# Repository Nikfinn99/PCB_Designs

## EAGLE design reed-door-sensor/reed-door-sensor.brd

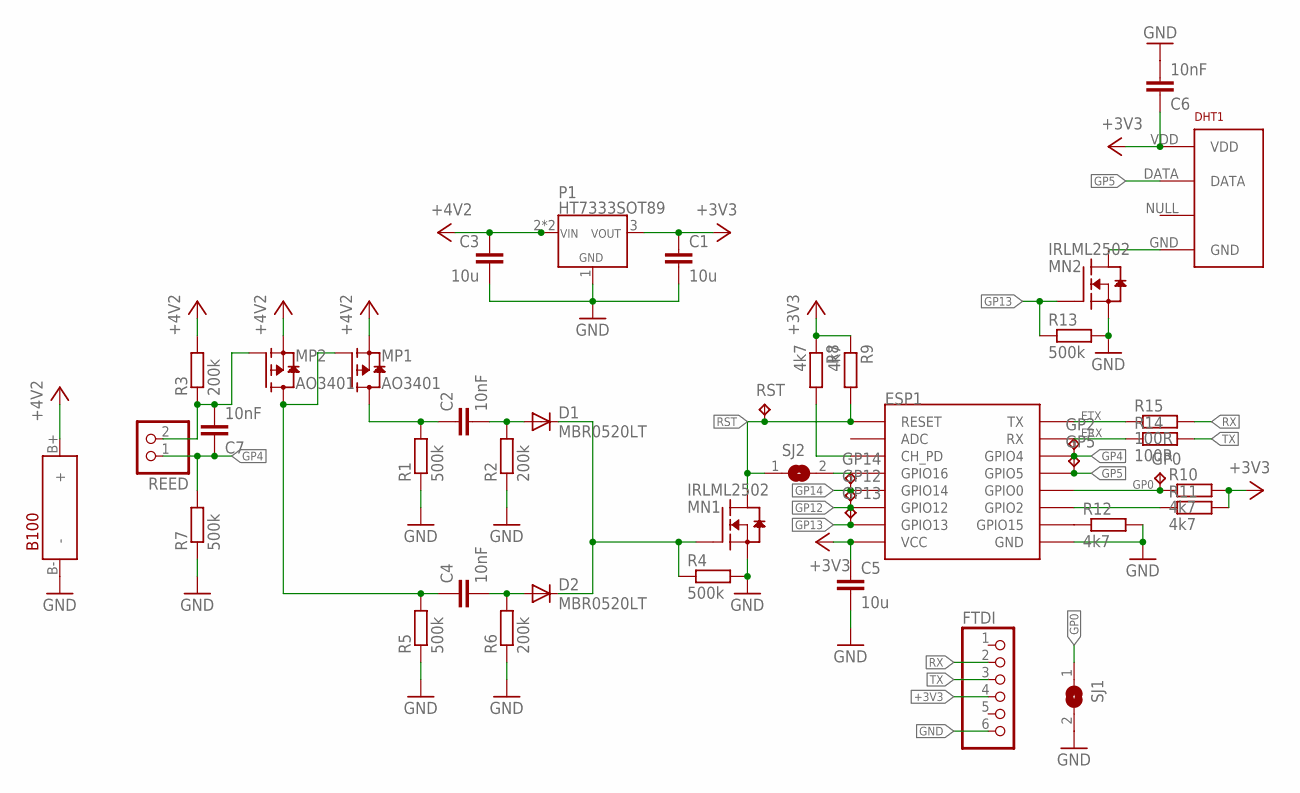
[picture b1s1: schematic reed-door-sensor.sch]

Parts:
B100: 18650_1X; 18650_HOLDER_1X
C1, C3, C5: 10u; C1206
C2, C4, C6, C7: 10nF; C0805
D1, D2: MBR0520LT; SOD123
DHT1: RHT03_DHT-22_AM2302; RHT03_DHT-22
ESP1: ESP12SMD; ESP12-SMD
FTDI: PINHD-1X06_2.54-S; 1X06-S
GP0: TPB2,54; B2,54
GP2, GP5, GP12, GP13, GP14: TPB1,27; B1,27
MN1, MN2: IRLML2502; SOT23
MP1, MP2: AO3401; SOT23
P1: HT7333SOT89; SOT89
R1, R4, R5, R7, R13: 500k; M0805
R2, R3, R6: 200k; M0805
R8, R9, R10, R11, R12: 4k7; M0805
R14, R15: 100R; M0805
REED: PINHD-1X02_2.54; 1X02
RST: TPB2,54; B2,54
SJ1, SJ2: SJ

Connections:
+3V3: C1.1, C5.1, C6.1, DHT1.VDD, ESP1.VCC, FTDI.4, P1.3 (VOUT), R8.1, R9.1, R10.2, R11.2
+5V: B100.B+ (+), C3.1, MP1.2 (S), MP2.2 (S), P1.2 (VIN), P1.2@1 (VIN), R3.2
ERX: ESP1.RXD0 (RX), R14.1
ETX: ESP1.TXD0 (TX), R15.1
GND: B100.B- (-), C1.2, C3.2, C5.2, C6.2, ESP1.GND, FTDI.6, MN1.2 (S), MN2.2 (S), P1.1 (GND), R1.1, R2.1, R4.2, R5.1, R6.1, R7.1, R12.2, R13.2, SJ1.2
GP0: ESP1.GPIO0, GP0.TP, R10.1, SJ1.1
GP4: C7.1, ESP1.GPIO4, GP2.TP, R7.2, REED.1
GP5: DHT1.DATA, ESP1.GPIO5, GP5.TP
GP12: ESP1.GPIO12, GP12.TP
GP13: ESP1.GPIO13, GP13.TP, MN2.1 (G), R13.1
GP14: ESP1.GPIO14, GP14.TP
unnamed: ESP1.GPIO16, SJ2.2
unnamed: ESP1.CH_PD, R8.2
unnamed: C2.2, D1.A, R2.2
unnamed: ESP1.GPIO15, R12.1
unnamed: ESP1.GPIO2, R11.1
unnamed: C4.2, D2.A, R6.2
unnamed: C2.1, MP1.3 (D), R1.2
unnamed: C4.1, MP1.1 (G), MP2.3 (D), R5.2
unnamed: D1.C, D2.C, MN1.1 (G), R4.1
unnamed: DHT1.GND, MN2.3 (D)
unnamed: C7.2, MP2.1 (G), R3.1, REED.2
RST: ESP1.RESET, MN1.3 (D), R9.2, RST.TP, SJ2.1
RX: FTDI.2, R15.2
TX: FTDI.3, R14.2

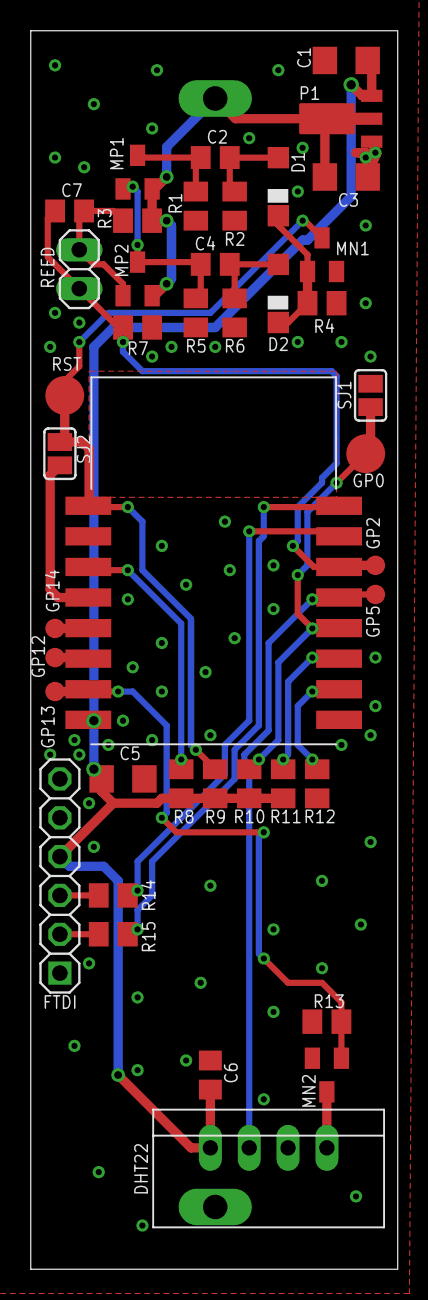
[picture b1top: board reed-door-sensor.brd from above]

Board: 2 copper layers, 24.0 x 81.0 mm, 43 parts (1 on the bottom side), 25 nets.

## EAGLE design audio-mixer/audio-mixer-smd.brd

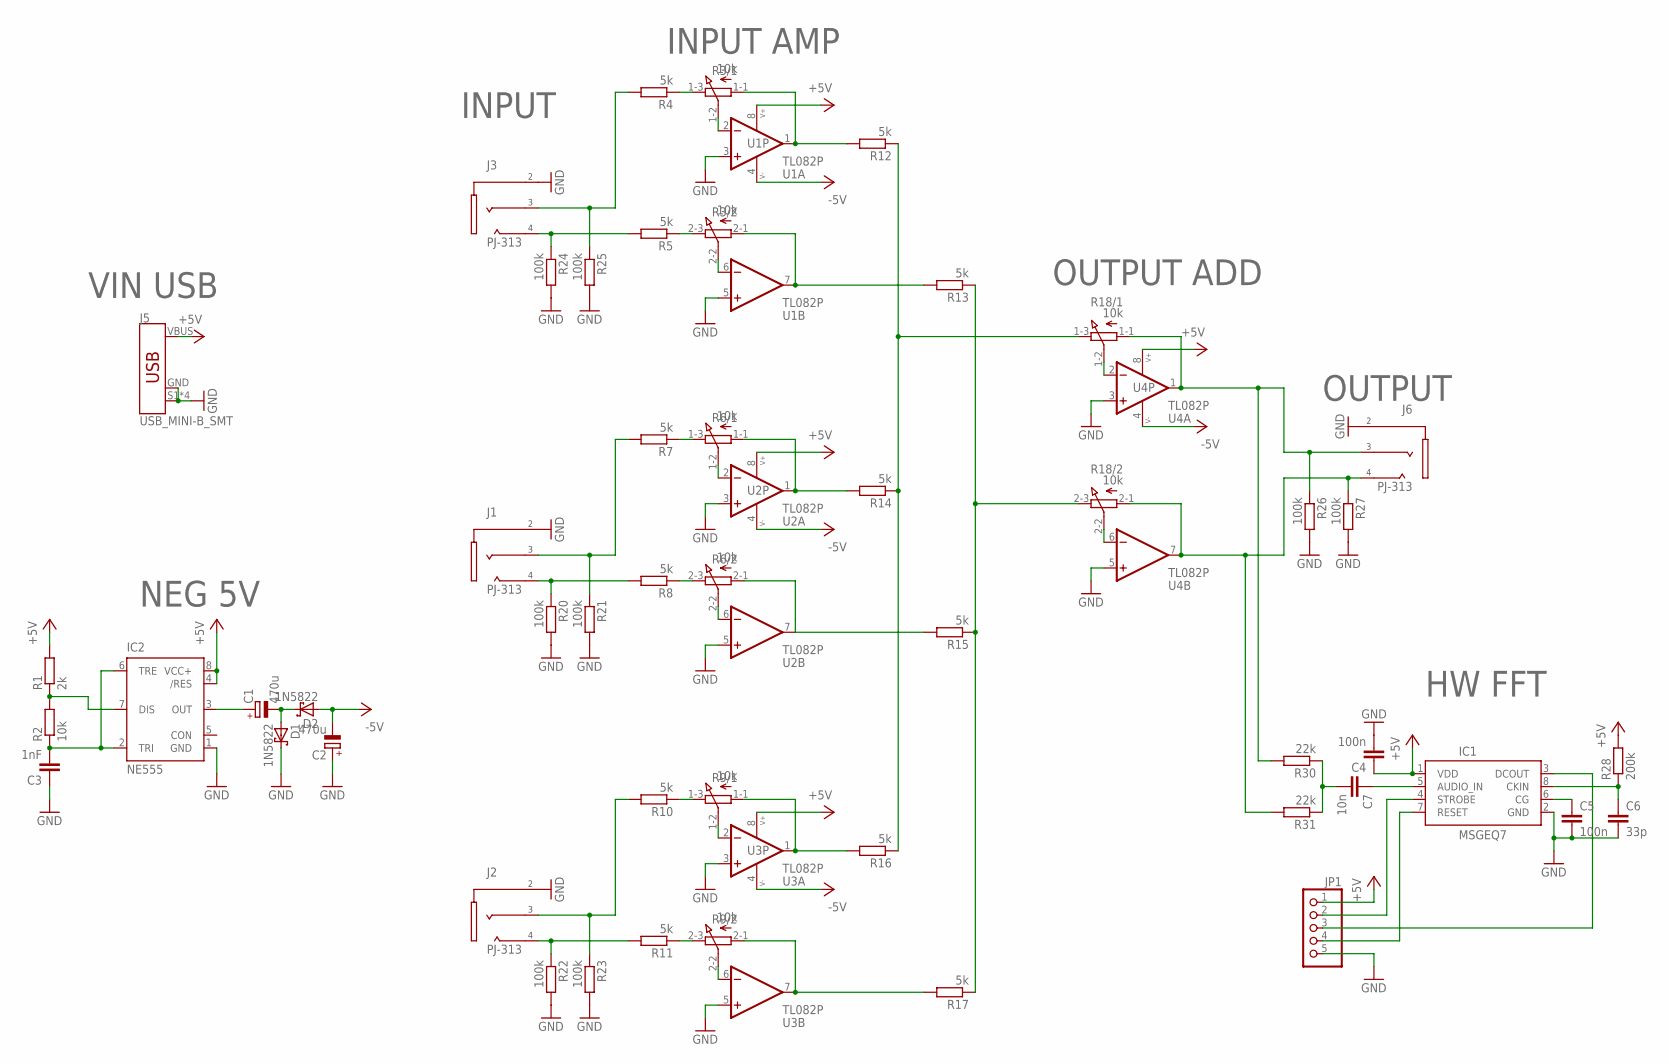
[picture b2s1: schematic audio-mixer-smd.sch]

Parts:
C1, C2: 470u; E5-8,5
C3: 1nF; C0805
C4, C5: 100n; C0805
C6: 33p; C0805
C7: 10n; C0805
D1, D2: 1N5822; DO41-7.6
IC1: MSGEQ7DIP; DIL08
IC2: NE555; DIL-08
J1, J2, J3, J6: PJ-313
J5: USB_MINI-B_SMT; USB-MINIB
JP1: PINHD-1X05_2.54-S; 1X05-S
R1: 2k; R0805
R2: 10k; R0805
R3, R6, R9, R18: 10k; 3RP/1610G
R4, R5, R7, R8, R10, R11, R12, R13, R14, R15, R16, R17: 5k; R0805
R20, R21, R22, R23, R24, R25, R26, R27: 100k; R0805
R28: 200k; R0805
R30, R31: 22k; R0805
U1, U2, U3, U4: TL082P; DIL08

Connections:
+5V: C4.1, IC1.1 (VDD), IC2.4 (/RES), IC2.8 (VCC+), J5.VBUS, JP1.1, R1.2, R28.2, U1.8 (V+), U2.8 (V+), U3.8 (V+), U4.8 (V+)
-5V: C2.-, D2.A, U1.4 (V-), U2.4 (V-), U3.4 (V-), U4.4 (V-)
GND: C2.+, C3.1, C4.2, C5.2, C6.2, D1.C, IC1.2 (GND), IC2.1 (GND), J1.2_1 (2), J1.2_2 (2), J2.2_1 (2), J2.2_2 (2), J3.2_1 (2), J3.2_2 (2), J5.GND, J5.S1 (SHIELD), J5.S2 (SHIELD), J5.S3 (SHIELD), J5.S4 (SHIELD), J6.2_1 (2), J6.2_2 (2), JP1.5, R20.2, R21.2, R22.2, R23.2, R24.2, R25.2, R26.2, R27.2, U1.3 (+IN), U1.5 (+IN), U2.3 (+IN), U2.5 (+IN), U3.3 (+IN), U3.5 (+IN), U4.3 (+IN), U4.5 (+IN)
unnamed: C3.2, IC2.2 (TRI), IC2.6 (TRE), R2.1
unnamed: IC2.7 (DIS), R1.1, R2.2
unnamed: R3.1-1 (A), R12.2, U1.1 (OUT)
unnamed: C1.-, D1.A, D2.C
unnamed: C1.+, IC2.3 (OUT)
unnamed: R3.1-2 (S), U1.2 (-IN)
unnamed: R3.2-1 (A), R13.2, U1.7 (OUT)
unnamed: R3.2-2 (S), U1.6 (-IN)
unnamed: R3.2-3 (E), R5.1
unnamed: R3.1-3 (E), R4.1
unnamed: J3.4_1 (4), J3.4_2 (4), R5.2, R24.1
unnamed: J3.3, R4.2, R25.1
unnamed: R6.1-1 (A), R14.2, U2.1 (OUT)
unnamed: R6.1-2 (S), U2.2 (-IN)
unnamed: R6.2-1 (A), R15.2, U2.7 (OUT)
unnamed: R6.2-2 (S), U2.6 (-IN)
unnamed: R6.2-3 (E), R8.1
unnamed: R6.1-3 (E), R7.1
unnamed: J1.4_1 (4), J1.4_2 (4), R8.2, R20.1
unnamed: J1.3, R7.2, R21.1
unnamed: R9.1-1 (A), R16.2, U3.1 (OUT)
unnamed: R9.1-2 (S), U3.2 (-IN)
unnamed: R9.2-1 (A), R17.2, U3.7 (OUT)
unnamed: R9.2-2 (S), U3.6 (-IN)
unnamed: R9.2-3 (E), R11.1
unnamed: R9.1-3 (E), R10.1
unnamed: J2.4_1 (4), J2.4_2 (4), R11.2, R22.1
unnamed: J2.3, R10.2, R23.1
unnamed: R12.1, R14.1, R16.1, R18.1-3 (E)
unnamed: R13.1, R15.1, R17.1, R18.2-3 (E)
unnamed: J6.3, R18.1-1 (A), R26.1, R30.2, U4.1 (OUT)
unnamed: J6.4_1 (4), J6.4_2 (4), R18.2-1 (A), R27.1, R31.2, U4.7 (OUT)
unnamed: R18.2-2 (S), U4.6 (-IN)
unnamed: R18.1-2 (S), U4.2 (-IN)
unnamed: C5.1, IC1.6 (CG)
unnamed: C6.1, IC1.8 (CKIN), R28.1
unnamed: C7.1, IC1.5 (AUDIO_IN)
unnamed: C7.2, R30.1, R31.1
unnamed: IC1.4 (STROBE), JP1.2
unnamed: IC1.7 (RESET), JP1.4
unnamed: IC1.3 (DCOUT), JP1.3

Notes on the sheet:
VIN USB
NEG 5V
INPUT AMP
OUTPUT ADD
OUTPUT
INPUT
HW FFT

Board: 2 copper layers, 50 parts (0 on the bottom side), 44 nets, no tracks yet.

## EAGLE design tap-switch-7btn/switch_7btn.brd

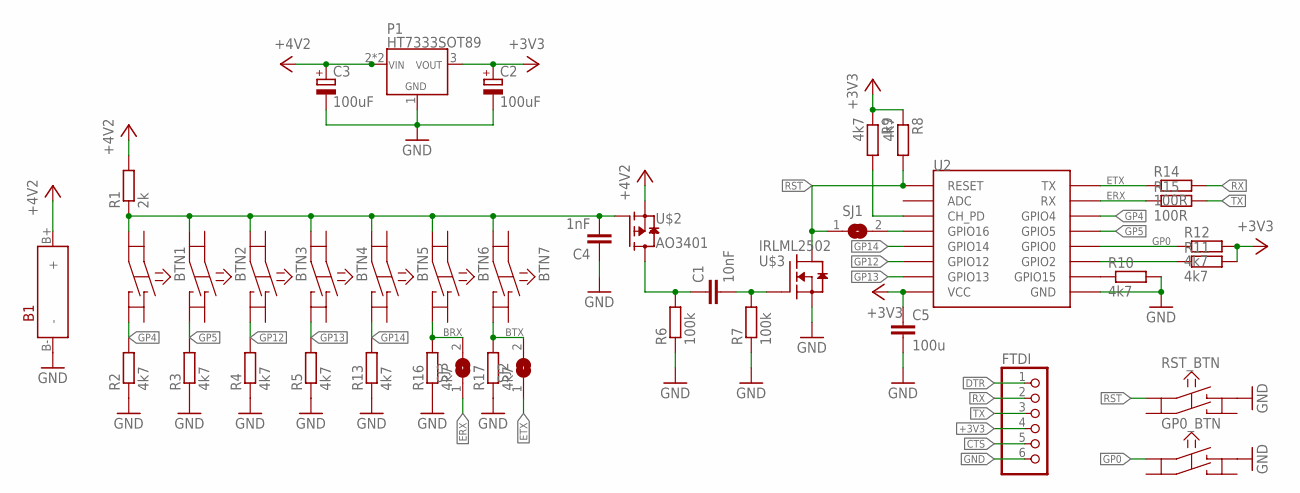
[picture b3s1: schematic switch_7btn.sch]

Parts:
B1: 18650_1X; 18650_HOLDER_1X
BTN1, BTN2, BTN3, BTN4, BTN5, BTN6, BTN7: KSM611A
C1: 10nF; C025-025X050
C2, C3: 100uF; E5-8,5
C4: 1nF; C025-025X050
C5: 100u; C1206
FTDI: PINHD-1X06_2.54-S; 1X06-S
GP0_BTN: KSM611A
P1: HT7333SOT89; SOT89
R1: 2k; MULTI_RESISTOR
R2, R3, R4, R5, R8, R9, R10, R11, R12, R13, R16, R17: 4k7; MULTI_RESISTOR
R6, R7: 100k; MULTI_RESISTOR
R14, R15: 100R; MULTI_RESISTOR
RST_BTN: KSM611A
SJ1, SJ2, SJ3: SJ
U2: ESP12SMD; ESP12-SMD
U$2: AO3401; SOT23
U$3: IRLML2502; SOT23

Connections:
+3V3: C2.+, C5.1, FTDI.4, P1.3 (VOUT), R8.1@1 (1), R8.1@2 (1), R9.1@1 (1), R9.1@2 (1), R11.2@1 (2), R11.2@2 (2), R12.2@1 (2), R12.2@2 (2), U2.VCC
+5V: B1.B+ (+), C3.+, P1.2 (VIN), P1.2@1 (VIN), R1.2@1 (2), R1.2@2 (2), U$2.2 (S)
BRX: BTN6.D, R16.2@1 (2), R16.2@2 (2), SJ3.2
BTX: BTN7.D, R17.2@1 (2), R17.2@2 (2), SJ2.2
CTS: FTDI.5
DTR: FTDI.1
ERX: R15.1@1 (1), R15.1@2 (1), SJ3.1, U2.RXD0 (RX)
ETX: R14.1@1 (1), R14.1@2 (1), SJ2.1, U2.TXD0 (TX)
GND: B1.B- (-), C2.-, C3.-, C4.1, C5.2, FTDI.6, GP0_BTN.B, P1.1 (GND), R2.1@1 (1), R2.1@2 (1), R3.1@1 (1), R3.1@2 (1), R4.1@1 (1), R4.1@2 (1), R5.1@1 (1), R5.1@2 (1), R6.1@1 (1), R6.1@2 (1), R7.1@1 (1), R7.1@2 (1), R10.2@1 (2), R10.2@2 (2), R13.1@1 (1), R13.1@2 (1), R16.1@1 (1), R16.1@2 (1), R17.1@1 (1), R17.1@2 (1), RST_BTN.B, U2.GND, U$3.2 (S)
GP0: GP0_BTN.A, R12.1@1 (1), R12.1@2 (1), U2.GPIO0
GP4: BTN1.D, R2.2@1 (2), R2.2@2 (2), U2.GPIO4
GP5: BTN2.D, R3.2@1 (2), R3.2@2 (2), U2.GPIO5
GP12: BTN3.D, R4.2@1 (2), R4.2@2 (2), U2.GPIO12
GP13: BTN4.D, R5.2@1 (2), R5.2@2 (2), U2.GPIO13
GP14: BTN5.D, R13.2@1 (2), R13.2@2 (2), U2.GPIO14
unnamed: SJ1.2, U2.GPIO16
unnamed: R9.2@1 (2), R9.2@2 (2), U2.CH_PD
unnamed: C1.2, R7.2@1 (2), R7.2@2 (2), U$3.1 (G)
unnamed: R10.1@1 (1), R10.1@2 (1), U2.GPIO15
unnamed: R11.1@1 (1), R11.1@2 (1), U2.GPIO2
unnamed: C1.1, R6.2@1 (2), R6.2@2 (2), U$2.3 (D)
unnamed: BTN1.C, BTN2.C, BTN3.C, BTN4.C, BTN5.C, BTN6.C, BTN7.C, C4.2, R1.1@1 (1), R1.1@2 (1), U$2.1 (G)
RST: R8.2@1 (2), R8.2@2 (2), RST_BTN.A, SJ1.1, U2.RESET, U$3.3 (D)
RX: FTDI.2, R14.2@1 (2), R14.2@2 (2)
TX: FTDI.3, R15.2@1 (2), R15.2@2 (2)

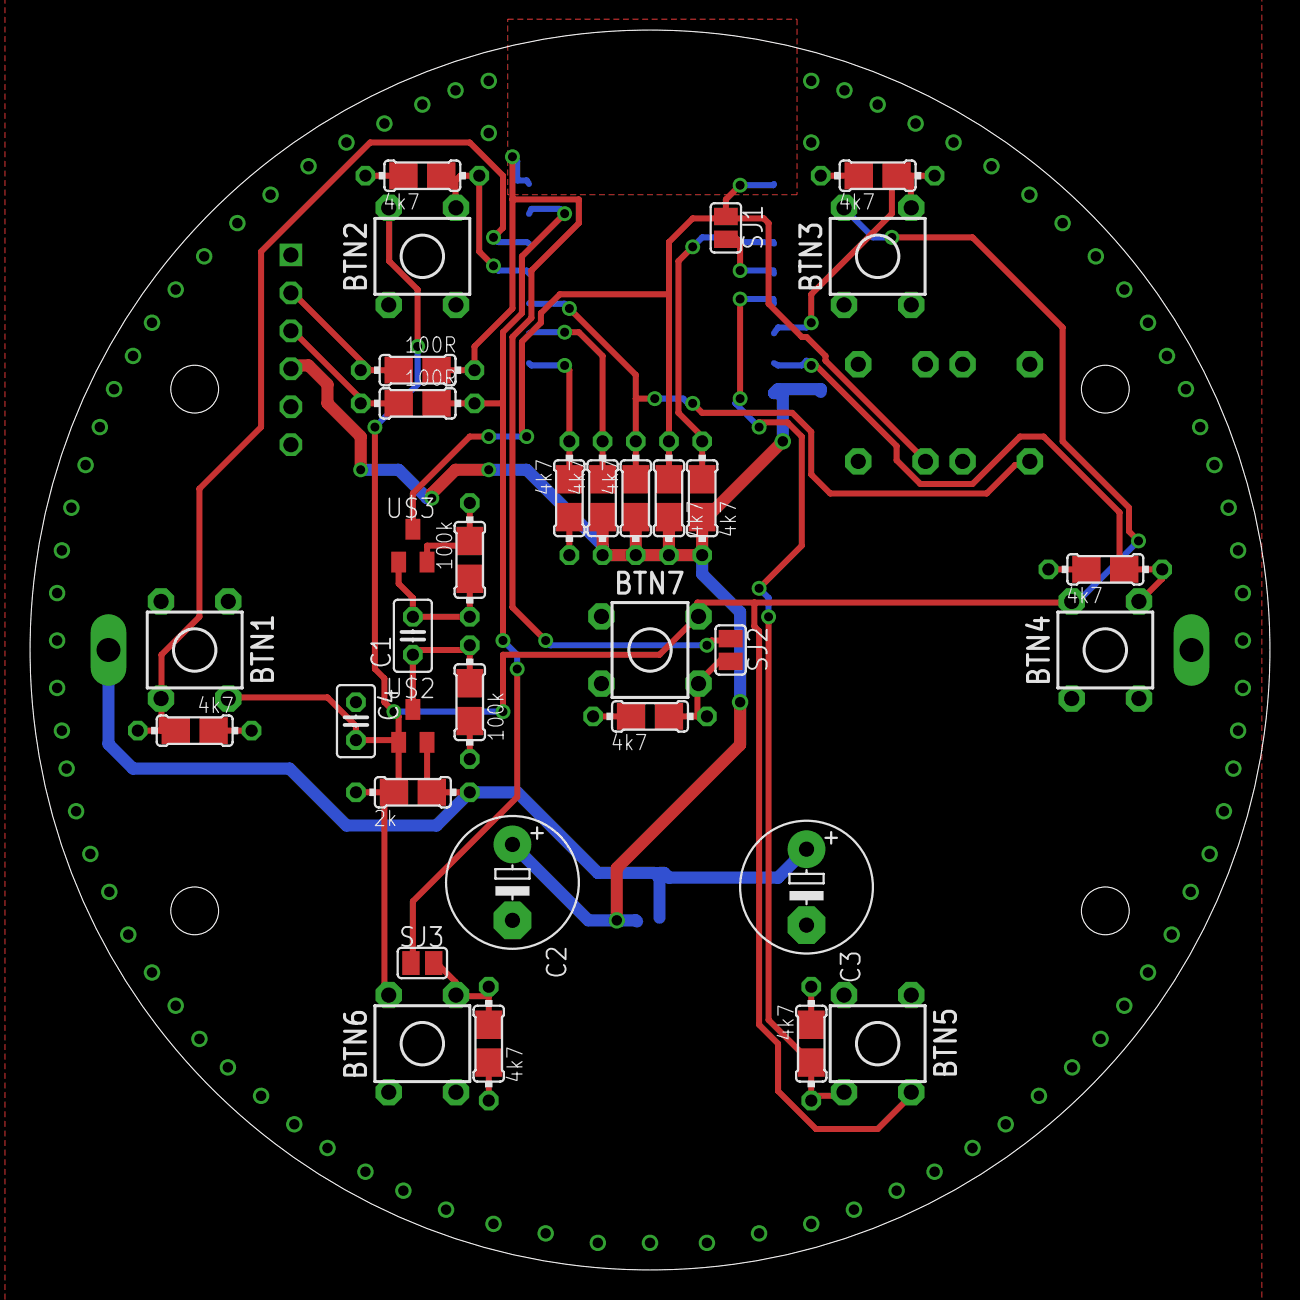
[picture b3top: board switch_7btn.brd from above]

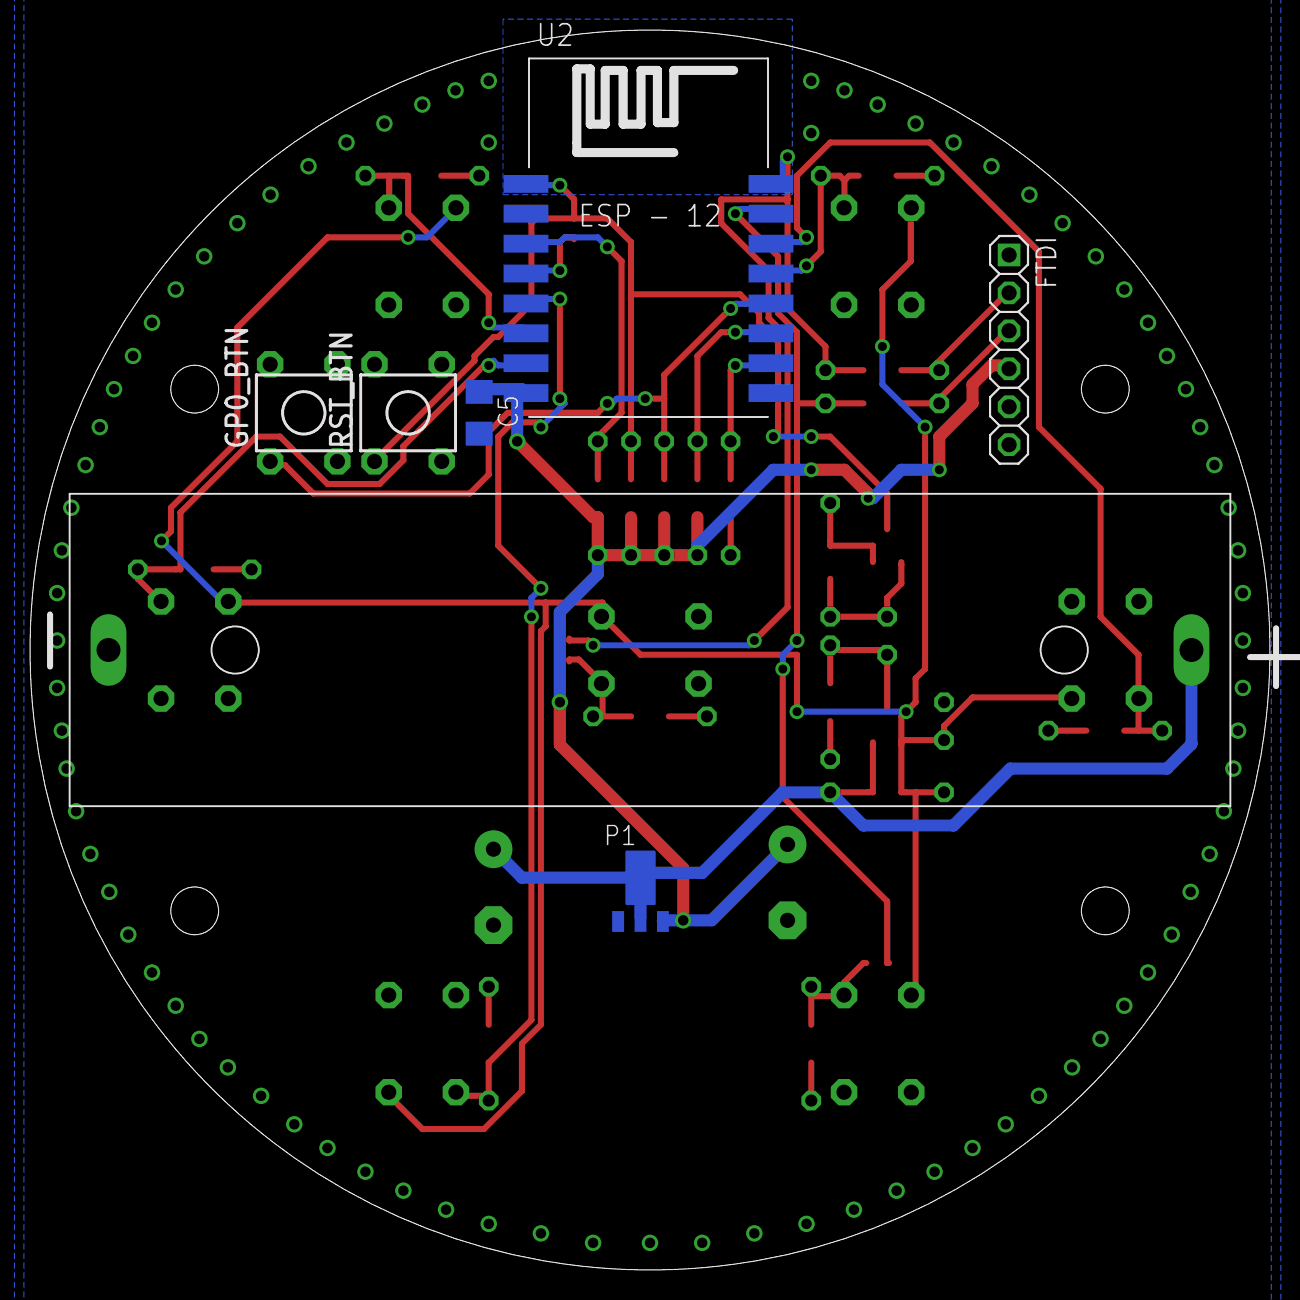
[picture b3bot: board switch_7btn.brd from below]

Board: 2 copper layers, 83.0 x 83.0 mm, 40 parts (7 on the bottom side), 23 nets.

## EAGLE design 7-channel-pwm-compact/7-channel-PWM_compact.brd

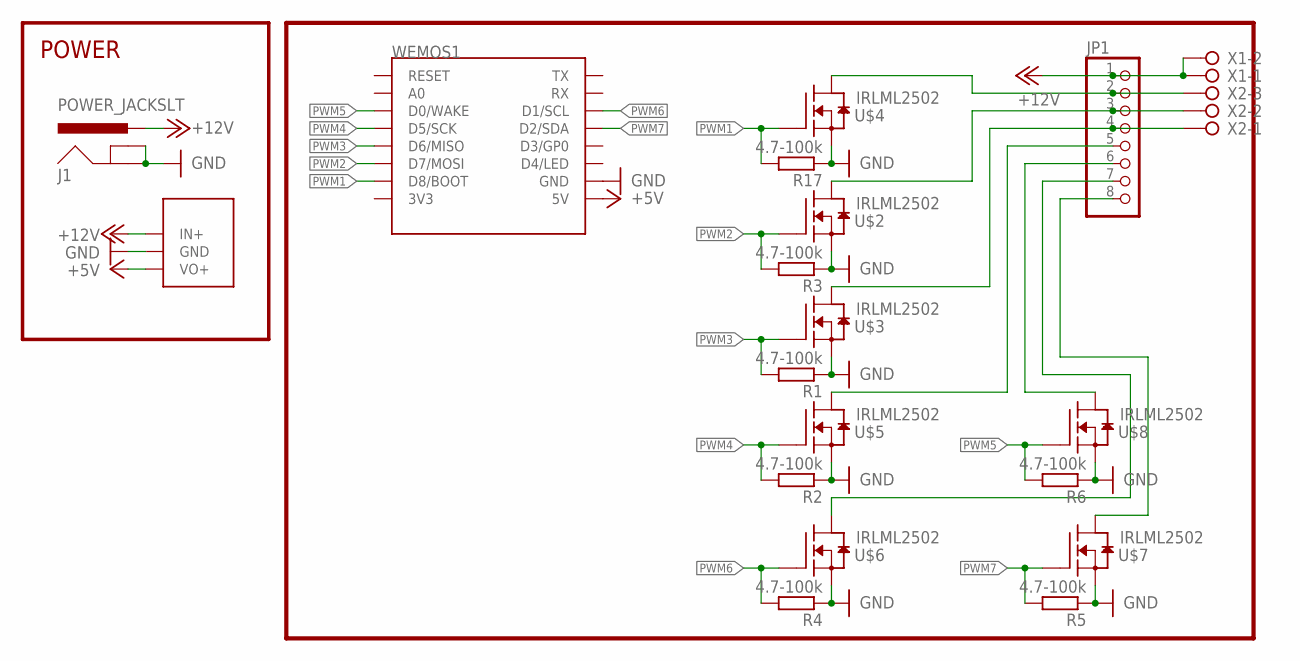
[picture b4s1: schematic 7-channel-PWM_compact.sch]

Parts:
J1: POWER_JACKSLT; POWER_JACK_SLOT
JP1: PINHD-1X08_2.54-S; 1X08-S
R1, R2, R3, R4, R5, R6, R17: 4.7-100k; R0805
U$1: BUCK_CONVERTER_TE818_VAR
U$2, U$3, U$4, U$5, U$6, U$7, U$8: IRLML2502; SOT23
WEMOS1: WEMOS-D1-MINI
X1: W237-02P; W237-132
X2: W237-03P; W237-133

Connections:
+5V: U$1.VO+, WEMOS1.5V
+12V: J1.PWR, JP1.1, U$1.IN+, X1.1, X1.2
GND: J1.GND@1 (GNDBREAK), J1.GND@2 (GND), R1.1, R2.1, R3.1, R4.1, R5.1, R6.1, R17.1, U$1.GND, U$2.2 (S), U$3.2 (S), U$4.2 (S), U$5.2 (S), U$6.2 (S), U$7.2 (S), U$8.2 (S), WEMOS1.GND
unnamed: JP1.2, U$4.3 (D), X2.3
unnamed: JP1.3, U$2.3 (D), X2.2
unnamed: JP1.4, U$3.3 (D), X2.1
unnamed: JP1.5, U$5.3 (D)
unnamed: JP1.6, U$8.3 (D)
unnamed: JP1.7, U$6.3 (D)
unnamed: JP1.8, U$7.3 (D)
PWM1: R17.2, U$4.1 (G), WEMOS1.D8 (D8/BOOT)
PWM2: R3.2, U$2.1 (G), WEMOS1.D7 (D7/MOSI)
PWM3: R1.2, U$3.1 (G), WEMOS1.D6 (D6/MISO)
PWM4: R2.2, U$5.1 (G), WEMOS1.D5 (D5/SCK)
PWM5: R6.2, U$8.1 (G), WEMOS1.D0 (D0/WAKE)
PWM6: R4.2, U$6.1 (G), WEMOS1.D1 (D1/SCL)
PWM7: R5.2, U$7.1 (G), WEMOS1.D2 (D2/SDA)

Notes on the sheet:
POWER

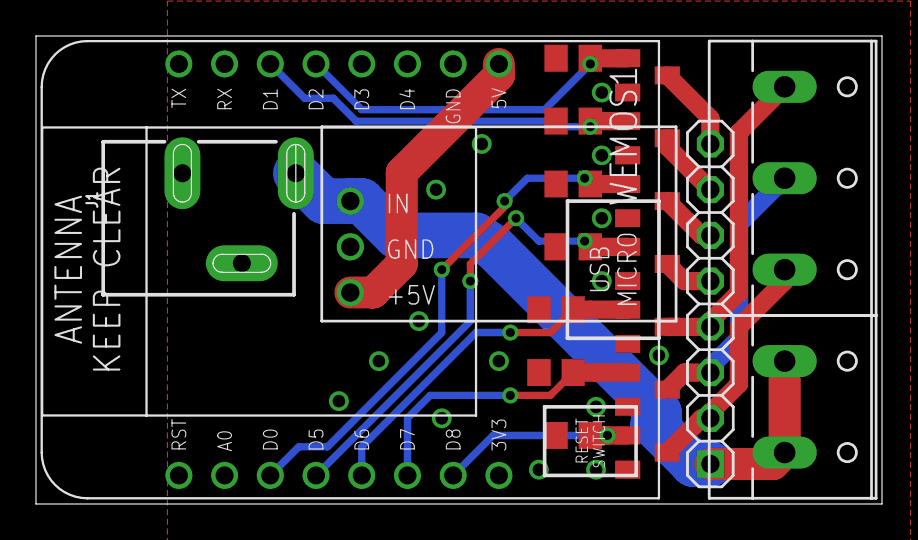
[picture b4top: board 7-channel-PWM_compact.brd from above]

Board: 2 copper layers, 47.0 x 26.0 mm, 20 parts (0 on the bottom side), 17 nets.

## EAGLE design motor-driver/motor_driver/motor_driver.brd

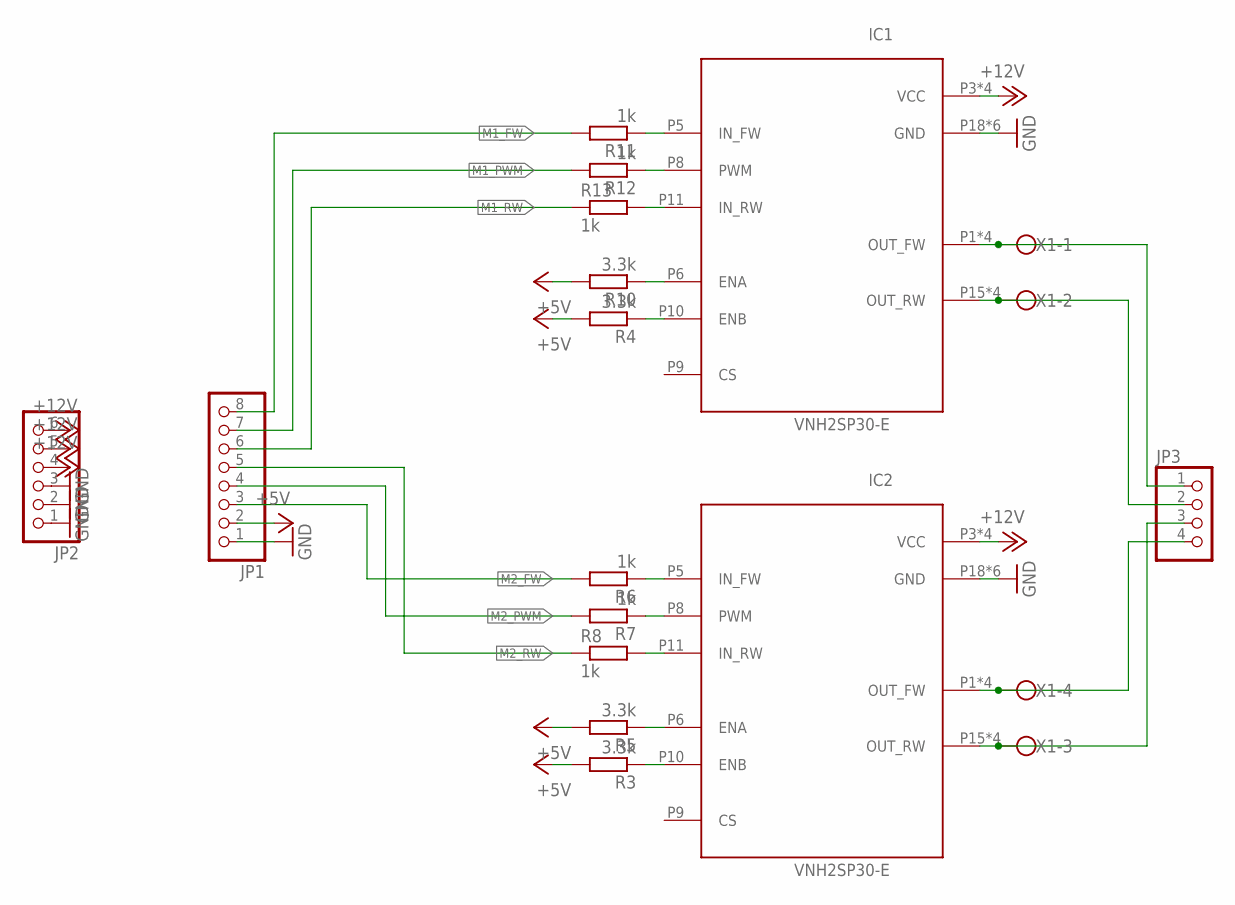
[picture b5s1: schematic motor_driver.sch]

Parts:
IC1, IC2: VNH2SP30-E; MP-SO-30
JP1: PINHD-1X08_2.54-S; 1X08-S
JP2: PINHD-1X06_2.54-S; 1X06-S
JP3: PINHD-1X04_2.54-S; 1X04-S
R3, R4, R5, R10: 3.3k; R0805
R6, R7, R8, R11, R12, R13: 1k; R0805
X1: KLEMME_4-PIN

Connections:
+5V: JP1.2, R3.2, R4.2, R5.2, R10.2
+12V: IC1.P3 (VCC), IC1.P13 (VCC), IC1.P23 (VCC), IC1.S1 (VCC), IC2.P3 (VCC), IC2.P13 (VCC), IC2.P23 (VCC), IC2.S1 (VCC), JP2.4, JP2.5, JP2.6
GND: IC1.P18 (GND), IC1.P19 (GND), IC1.P20 (GND), IC1.P26 (GND), IC1.P27 (GND), IC1.P28 (GND), IC2.P18 (GND), IC2.P19 (GND), IC2.P20 (GND), IC2.P26 (GND), IC2.P27 (GND), IC2.P28 (GND), JP1.1, JP2.1, JP2.2, JP2.3
M1_FW: JP1.8, R11.2
M1_PWM: JP1.7, R12.2
M1_RW: JP1.6, R13.1
M2_FW: JP1.3, R6.2
M2_PWM: JP1.4, R7.2
M2_RW: JP1.5, R8.1
unnamed: IC2.P5 (IN_FW), R6.1
unnamed: IC2.P6 (ENA), R5.1
unnamed: IC1.P5 (IN_FW), R11.1
unnamed: IC2.P10 (ENB), R3.1
unnamed: IC2.P8 (PWM), R7.1
unnamed: IC1.P6 (ENA), R10.1
unnamed: IC1.P10 (ENB), R4.1
unnamed: IC1.P8 (PWM), R12.1
unnamed: IC1.P11 (IN_RW), R13.2
unnamed: IC1.P1 (OUT_FW), IC1.P25 (OUT_FW), IC1.P30 (OUT_FW), IC1.S2 (OUT_FW), JP3.1, X1.1
unnamed: IC1.P15 (OUT_RW), IC1.P16 (OUT_RW), IC1.P21 (OUT_RW), IC1.S3 (OUT_RW), JP3.2, X1.2
unnamed: IC2.P11 (IN_RW), R8.2
unnamed: IC2.P15 (OUT_RW), IC2.P16 (OUT_RW), IC2.P21 (OUT_RW), IC2.S3 (OUT_RW), JP3.3, X1.3
unnamed: IC2.P1 (OUT_FW), IC2.P25 (OUT_FW), IC2.P30 (OUT_FW), IC2.S2 (OUT_FW), JP3.4, X1.4

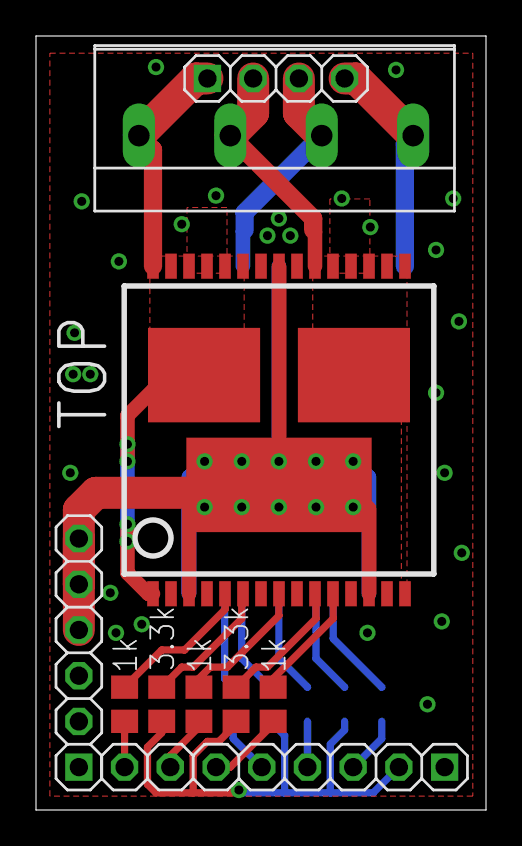
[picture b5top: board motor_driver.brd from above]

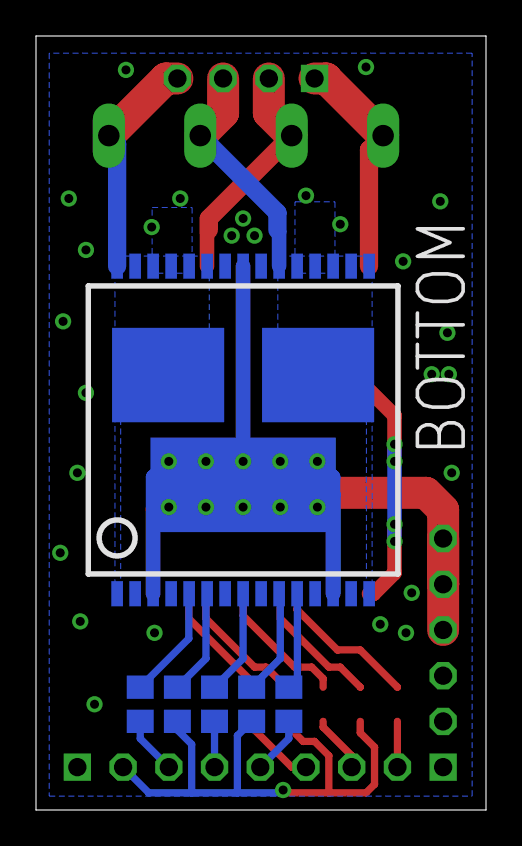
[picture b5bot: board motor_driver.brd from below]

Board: 2 copper layers, 25.0 x 43.0 mm, 16 parts (6 on the bottom side), 23 nets.

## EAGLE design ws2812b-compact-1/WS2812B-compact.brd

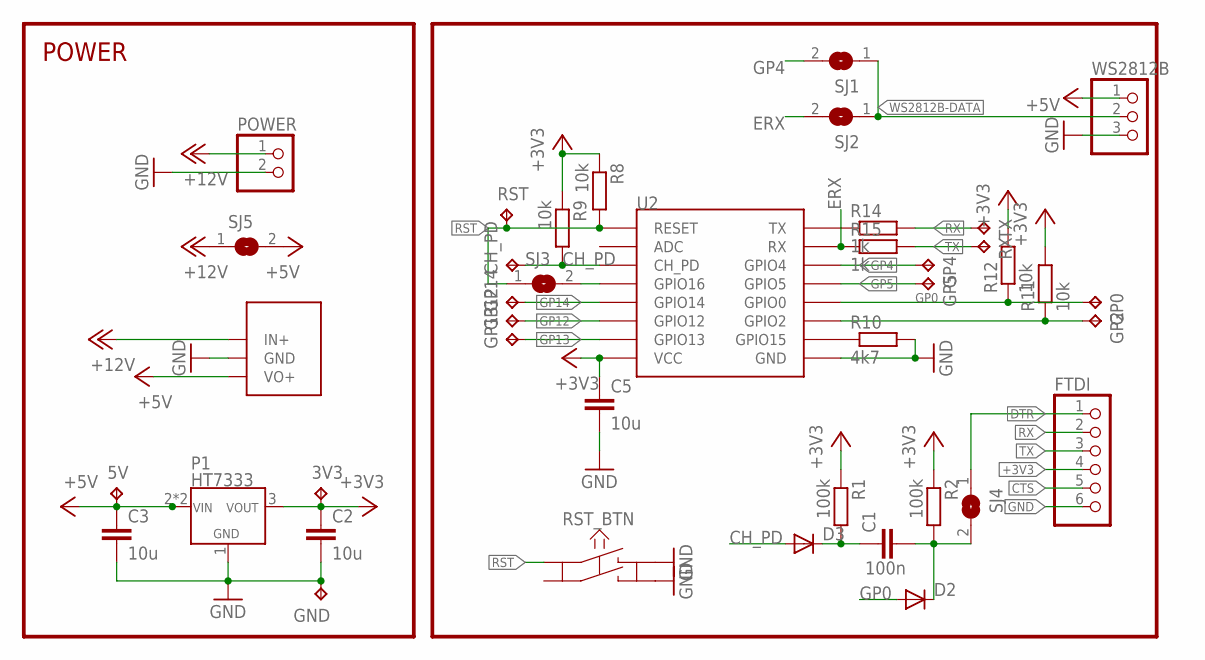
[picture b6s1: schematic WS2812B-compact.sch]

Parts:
3V3, 5V: TPB2,54; B2,54
C1: 100n; C1206
C2, C3, C5: 10u; C1206
CH_PD: TPB1,27; B1,27
D2, D3: DIODE-MINIMELF; MINIMELF
FTDI: PINHD-1X06_2.54-S; 1X06-S
GND: TPB2,54; B2,54
GP0, GP2, GP4, GP5, GP12, GP13, GP14: TPB1,27; B1,27
P1: HT7333; SOT89
POWER: PINHD-1X2; 1X02
R1, R2: 100k; R0805
R8, R9, R11, R12: 10k; R0805
R10: 4k7; R0805
R14, R15: 1k; R0805
RST: TPB1,27; B1,27
RST_BTN: KSM611A
RX: TPB1,27; B1,27
SJ1, SJ2, SJ3, SJ4, SJ5: SJ
TX: TPB1,27; B1,27
U2: ESP12SMD; ESP12-SMD
U$1: BUCK_CONVERTER_TE818_VAR
WS2812B: PINHD-1X03_2.54-S; 1X03-S

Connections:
+3V3: 3V3.TP, C2.1, C5.1, FTDI.4, P1.3 (VOUT), R1.1, R2.1, R8.1, R9.1, R11.2, R12.2, U2.VCC
+5V: 5V.TP, C3.1, P1.2 (VIN), P1.2@1 (VIN), SJ5.2, U$1.VO+, WS2812B.1
+12V: POWER.1, SJ5.1, U$1.IN+
CH_PD: CH_PD.TP, D3.A, R9.2, U2.CH_PD
CTS: FTDI.5
DTR: FTDI.1, SJ4.1
ERX: R15.1, SJ2.2, U2.RXD0 (RX)
GND: C2.2, C3.2, C5.2, FTDI.6, GND.TP, P1.1 (GND), POWER.2, R10.2, RST_BTN.B, RST_BTN.D, U2.GND, U$1.GND, WS2812B.3
GP0: D2.A, GP0.TP, R12.1, U2.GPIO0
GP4: GP4.TP, SJ1.2, U2.GPIO4
GP5: GP5.TP, U2.GPIO5
GP12: GP12.TP, U2.GPIO12
GP13: GP13.TP, U2.GPIO13
GP14: GP14.TP, U2.GPIO14
unnamed: C1.2, D2.C, R2.2, SJ4.2
unnamed: C1.1, D3.C, R1.2
unnamed: R10.1, U2.GPIO15
unnamed: GP2.TP, R11.1, U2.GPIO2
unnamed: SJ3.2, U2.GPIO16
unnamed: R14.1, U2.TXD0 (TX)
RST: R8.2, RST.TP, RST_BTN.A, SJ3.1, U2.RESET
RX: FTDI.2, R14.2, TX.TP
TX: FTDI.3, R15.2, RX.TP
WS2812B-DATA: SJ1.1, SJ2.1, WS2812B.2

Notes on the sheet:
POWER

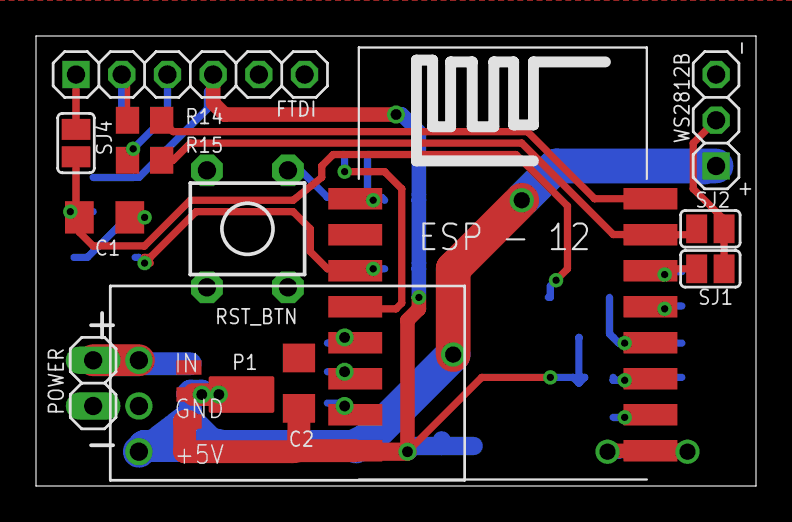
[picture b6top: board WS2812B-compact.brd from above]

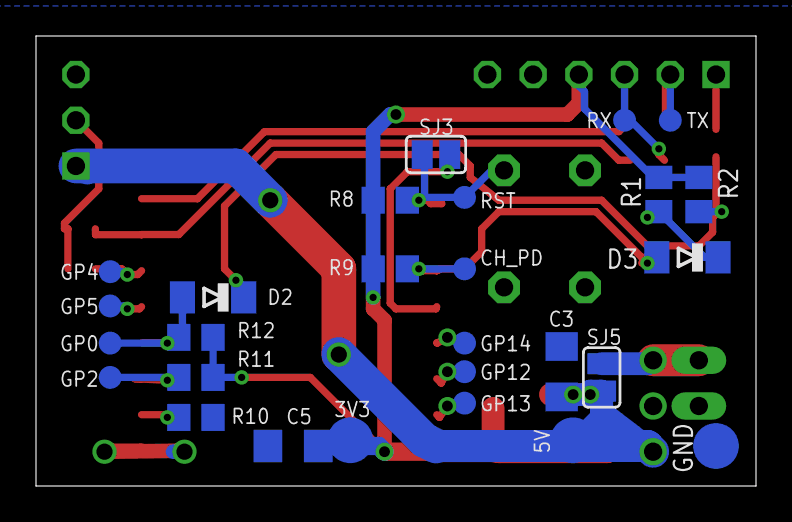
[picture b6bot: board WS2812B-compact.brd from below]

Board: 2 copper layers, 40.0 x 25.0 mm, 41 parts (27 on the bottom side), 23 nets.

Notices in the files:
parts and their libraries:
SparkFun-Connectors: Licensing: Creative Commons ShareAlike 4.0 International - https://creativecommons.org/licenses/by-sa/4.0
op-amp: Copyright (C) 2006 by Bob Starr
